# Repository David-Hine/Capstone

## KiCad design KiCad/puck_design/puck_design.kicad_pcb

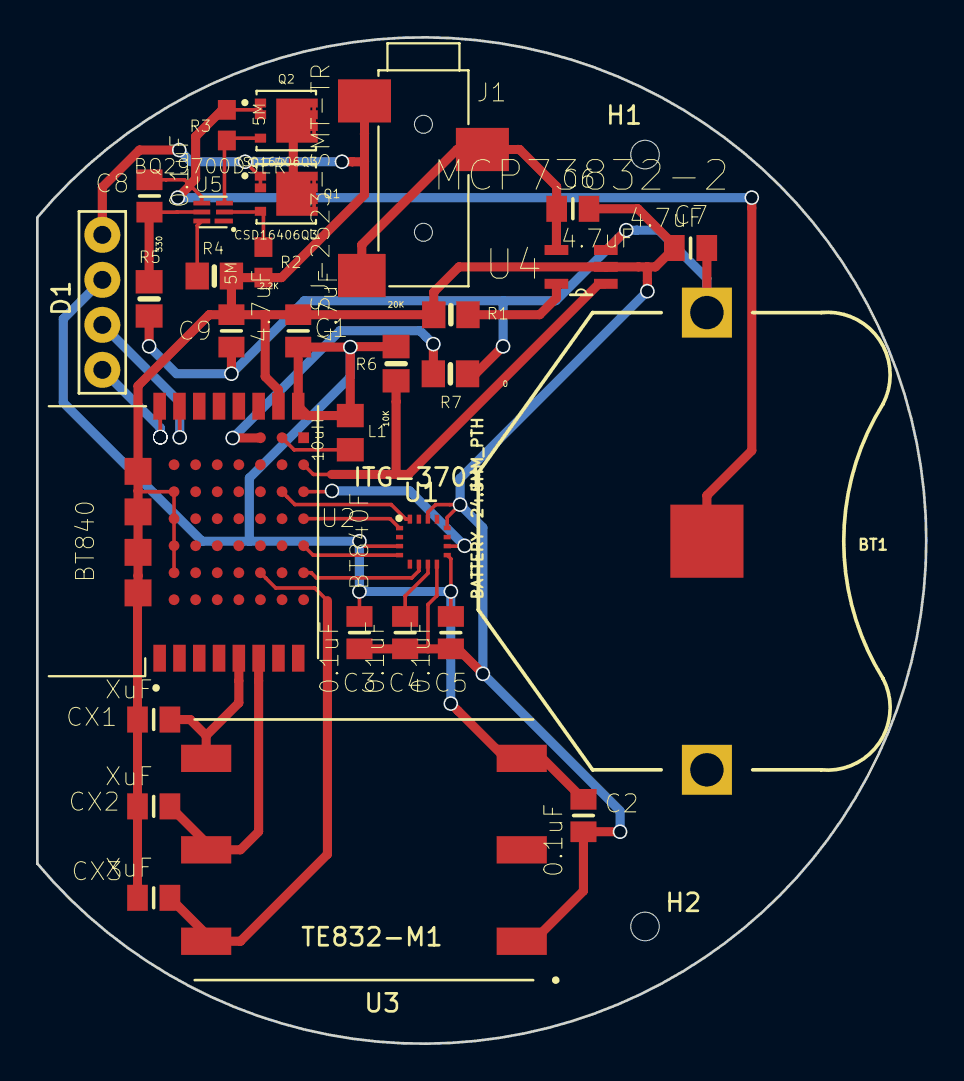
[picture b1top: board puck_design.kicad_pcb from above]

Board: 2 copper layers, 49.4 x 55.9 mm, 32 parts (0 on the bottom side), 25 nets.

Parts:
BT1: BATTERY-24.5MM_PTH; BATTCON_24.5MM_PTH
C1, C6, C7, C9: 4.7uF; CAPC2012X140N
C2, C3, C4, C5, C8: 0.1uF; CAPC2012X140N
CX1, CX2, CX3: XuF; CAPC2012X140N
D1: Debug; Debug Header
H1, H2: Mounting Hole
J1: SJ-2523-SMT-TR; CUI_SJ-2523-SMT-TR
L1: 10uH; CAPC2012X135N
Q1, Q2: CSD16406Q3
R1: 20K; 0805-NO
R2, R3: 5M; RESC1608X55
R4: 2.2K; 0805-NO
R5: 330; 0805-NO
R6: 10K; 0805-NO
R7: 0; 0805-NO
U1: ITG-3701
U2: BT840F
U3: TE832-M1; 832M1
U4: MCP73832-2; MCP73832T_2ATI_OT
U5: BQ29700DSER

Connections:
+BATT: BT1.1, C7.1, C9.1, R5.1, R7.2, U4.3
GND: C1.2, C2.2, C3.2, C4.2, C5.2, C6.2, C7.2, C9.2, CX1.2, CX2.2, CX3.2, D1.4, J1.1, Q1.1, Q1.2, R1.2, R2.2, R4.2, U1.8, U1.12, U1.14, U2.10, U2.A0, U2.B0, U2.C0, U2.D0, U2.F0, U2.F1, U2.F2, U2.F3, U3.3, U4.2
unnamed: BT1.2, C8.2, Q2.1, Q2.2, R3.2, U5.4
unnamed: C4.1, U1.7
unnamed: C6.1, J1.2, J1.3, U4.4
unnamed: C8.1, R5.2, U5.5
unnamed: CX1.1, U2.5, U3.6
unnamed: CX2.1, U2.6, U3.5
unnamed: CX3.1, U2.A4, U3.4
unnamed: D1.1, U2.16
unnamed: D1.2, U2.15
unnamed: L1.2, U2.F5
unnamed: Q1.4, R2.1, U5.2
unnamed: Q1.9, Q2.9
unnamed: Q2.4, R3.1, U5.3
unnamed: R1.1, U4.5
unnamed: R4.1, U5.6
unnamed: R6.2, U2.E6, U4.1
unnamed: R7.1, U2.F4
unnamed: U1.1, U2.C6
unnamed: U1.4, U2.B6
unnamed: U1.6, U2.A6
unnamed: U1.10, U2.D6
unnamed: U1.16, U2.D5
VCC: C1.1, C2.1, C3.1, C5.1, D1.3, L1.1, R6.1, U1.3, U1.9, U2.9, U3.1

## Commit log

2018-11-20 Inital commit
2018-11-20 Changed library name
2018-11-21 added nRF52840 to library
2018-11-21 added connections according to config no 4
2018-11-22 corrected errors
2018-11-22 Added connections for accelerometer
2018-11-22 Removed USB features, added battery (VDDH) to schem
2018-11-22 Initial gyro connections
2018-11-23 Added antenna, cap and resistor. Annotated schem
2018-11-23 Added remaining connections for gyro
2018-11-23 but wait, there's more!
2018-11-30 Fixed gyro connections
2018-12-04 Added BT840F module to custom library
2018-12-04 Updated schem. Replaced nRF52840 with BT840F
2018-12-14 Rearranged circuit and added MCP73831-2
2018-12-14 Added battery holder and connector
2018-12-17 Cleaned up circuit diagram
2018-12-19 Remove capacitor at connector
2018-12-20 Added extra decoupling caps
2018-12-20 Added battery protection IC, resistors and MOS
2019-01-04 Added footprint library
2019-01-07 Added BLE example and SDK folders
2019-01-08 Rearranged battery protection circuitry and added missing components
2019-01-09 Added footprints and associated to symbols
2019-01-09 Changed pinout of accelerometer (X, Y) and charger IC status (to pin D6)
2019-01-10 Added inductor footprint
2019-01-10 Added custom header for BT840F under \nRF5_SDK_Current\components\boards
2019-01-11 Added ble_lightbulb_remote_control (client) and ble_puck project folders
2019-01-14 Added SDK 15.0.0 (for example ble_app_uart_SAADC)
2019-01-15 Removed SDK 15.0.0
2019-01-21 Updated schematic and added PCB layout with gerber/drill files
2019-01-22 Added mounting holes and updated gerber/drill files
2019-01-24 Because I forgot
2019-01-28 Added SAADC service in ble_puck project
2019-01-29 Added SAADC service to ble_app_uart_and_saadc (and removed it from ble_puck)
2019-02-03 Added battery service to ble_app_uart_and_saadc project
2019-02-04 Demo ready
2019-02-18 Sampling and transmitting at 5 kHz
2019-02-22 Added UI folder
2019-03-03 Added JS code for UI, modified advertising name to BLE_Puck
2019-03-08 JS puck_test
2019-03-11 JS puck_test2
2019-03-12 Added good JS command line UI puck.js
2019-03-12 Good puck.js
2019-03-14 Cleanup of BLE Projects folder-removed old projects, renamed good one
2019-03-17 Updated puck.js for CSV
2019-03-21 Getting close...
2019-03-23 Updated ble_puck and puck.js
2019-03-24 eric's commit
2019-03-25 Updated puck.js, battery calculations
2019-03-27 did this work
2019-03-28 PUSHH
2019-04-01 final test
2019-04-05 Final BLE_Puck project
2019-04-26 Added documentation
2019-04-26 Updated pc-ble-driver
2019-04-26 Updated documentation
2019-04-26 Updated procedure
2019-04-29 Added pics of jig for cutting puck
2019-04-30 Added tutorials and datasheets/manuals for components
2020-03-06 `vallen` is verified to be less than `len`, therefore, it can never be the case that `vallen >= len + sizeof(rhostname)`.
    This PR fixes the check so the `rhostname` array does not overflow.
    Reported-by: Github Security Lab <securitylab@github.com>
